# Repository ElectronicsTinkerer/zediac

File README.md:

# ZEDIA Computer System

(Zach's Electronic Desktop Instrumentation and Analysis Computer)

![Top-down photo of the PCB. From left to right: GPIO connector, VIA, CPU, RAM, ROM, DUART. Below the CPU RAM and ROM are several 74xx series ICs for address decoding. The right edge of the PCB features the power and USB connectors. Note the incorrect date on the PCB-when I changed the date over from December, 2022 to January 2023, I managed to change the month and date, but not the year. Oops](./pcb1.0.jpg)

## System stats

* W65C816 CPU
* 32k EEPROM (with write capability)
* 512K RAM
* 65C22 VIA, providing ~20 GPIOs (really 16 + 4 handshake lines)
* ST16C2752 Dual UART
* 5+ MHz operation
* Partial system bus expansion header with address decoding
* USB-C UART interface via a CP2102
* 2 power delivery methods (unregulated voltage in via barrel jack or terminal block. Also power over USB)
* ESD protection on all IO headers

## Software

All software is available in the `software` directory. At the moment, there is a system monitor which provides many memory manipulation utilities.

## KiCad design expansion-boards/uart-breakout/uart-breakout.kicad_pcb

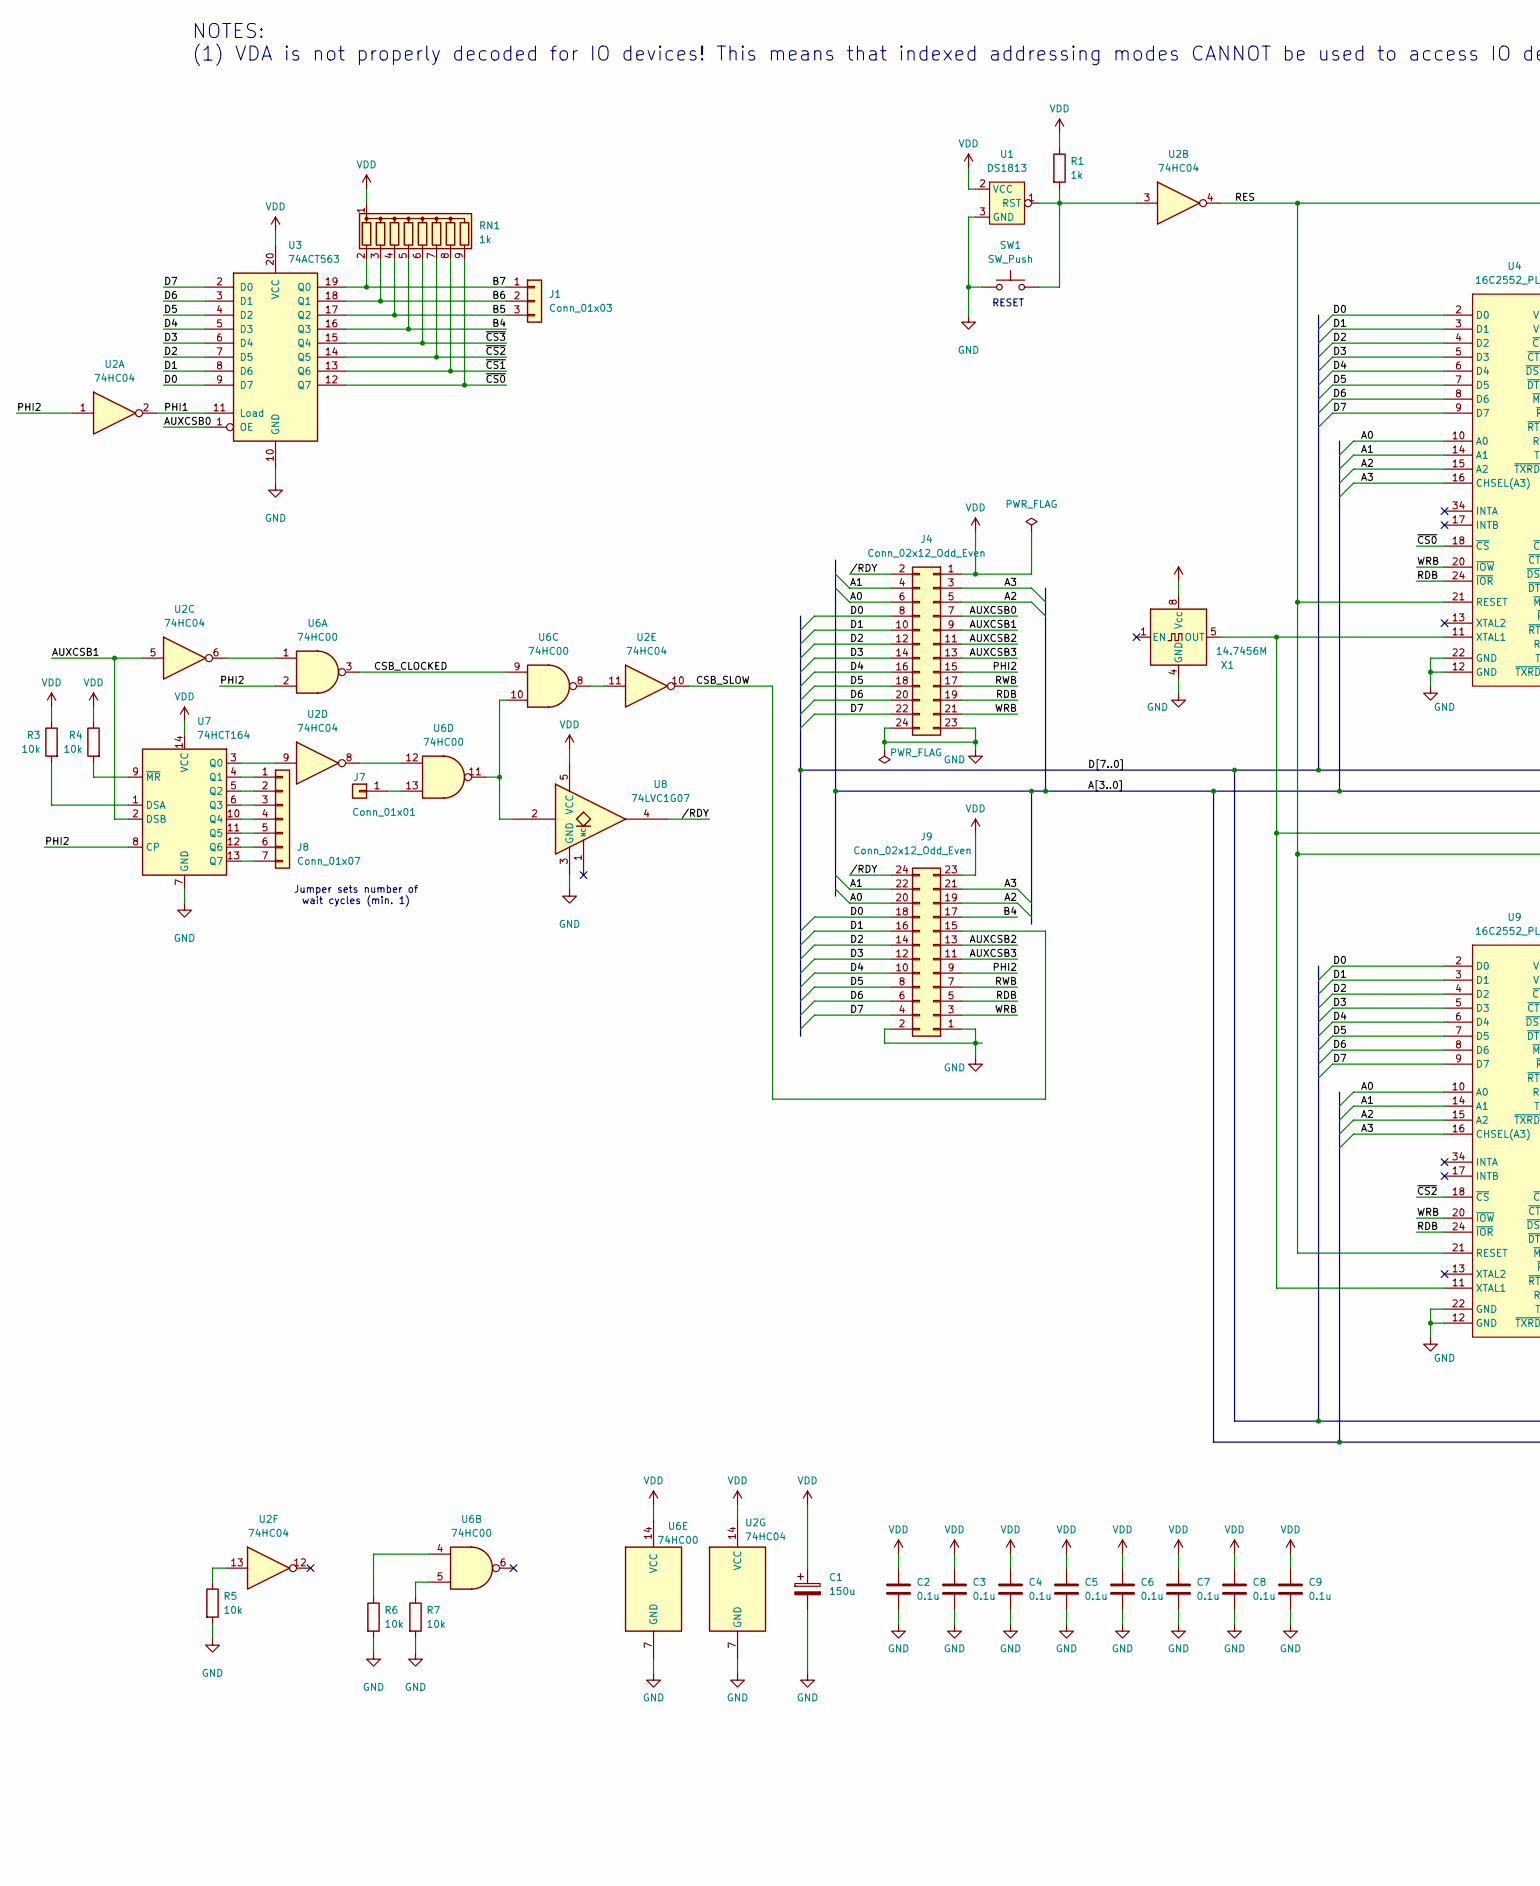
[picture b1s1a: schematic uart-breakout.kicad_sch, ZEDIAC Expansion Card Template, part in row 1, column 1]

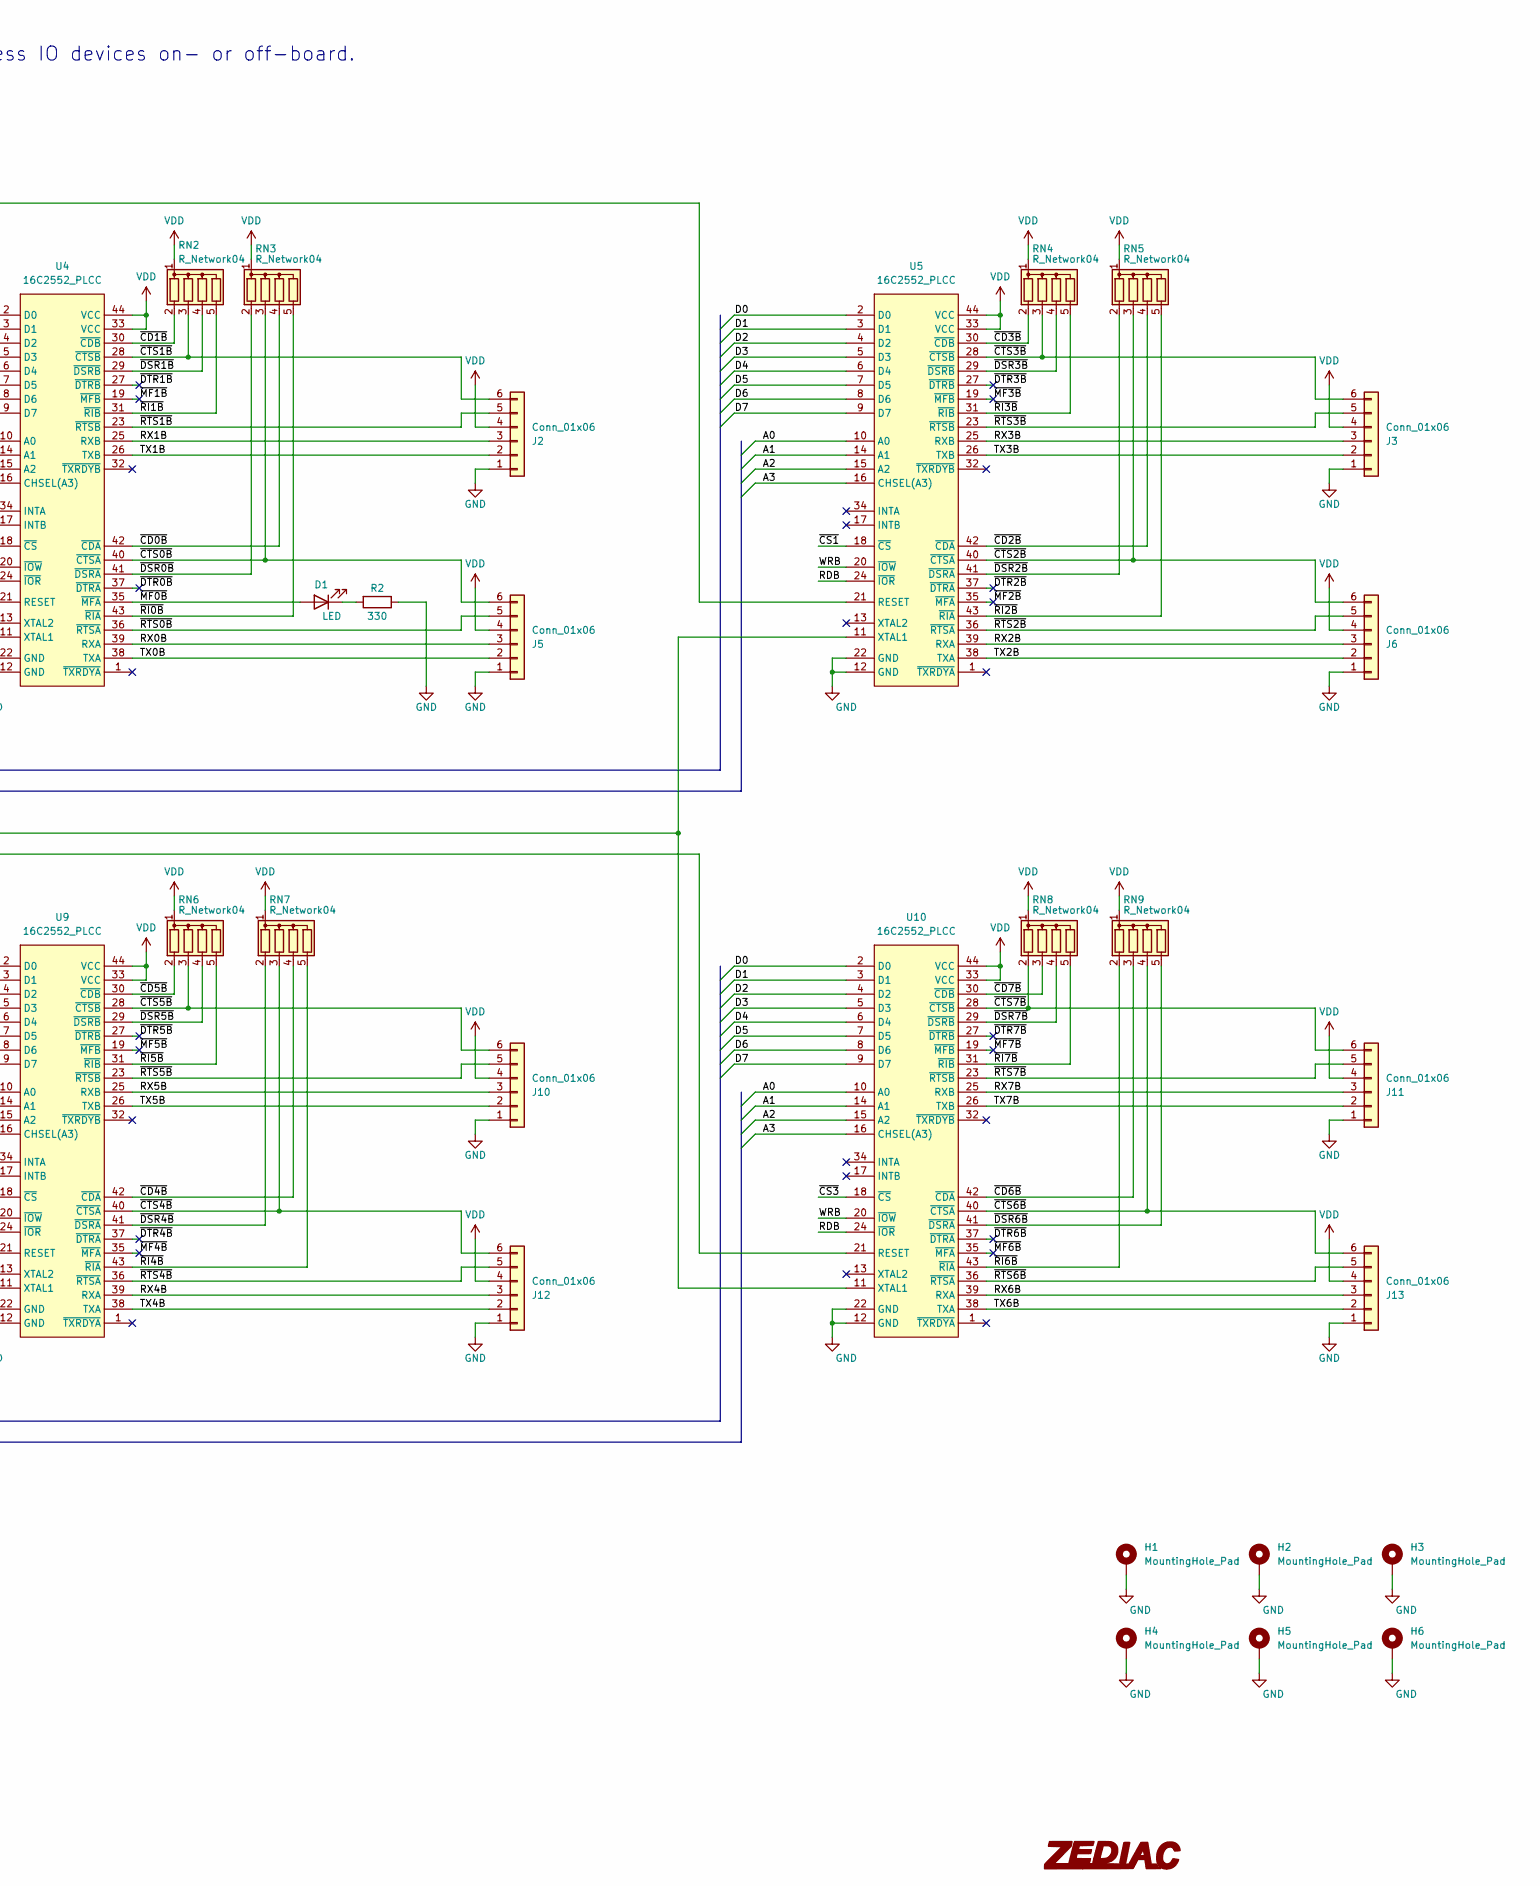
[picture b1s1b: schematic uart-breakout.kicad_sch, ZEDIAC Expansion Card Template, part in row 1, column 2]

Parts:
C1: 150u; C_Radial_D8.0mm_H7.0mm_P3.50mm
C2, C3, C4, C5, C6, C7, C8, C9: 0.1u; C_Disc_D4.3mm_W1.9mm_P5.00mm
D1: LED; LED_D5.0mm
G1: LOGO; zediac-logo
H1, H2, H3, H4, H5, H6: MountingHole_Pad; MountingHole_3.2mm_M3_Pad
J1: Conn_01x03; PinSocket_1x03_P2.54mm_Vertical
J2, J3, J5, J6, J10, J11, J12, J13: Conn_01x06; PinSocket_1x06_P2.54mm_Vertical
J4, J9: Conn_02x12_Odd_Even; PinSocket_2x12_P2.54mm_Vertical
J7: Conn_01x01; PinSocket_1x01_P2.54mm_Vertical
J8: Conn_01x07; PinSocket_1x07_P2.54mm_Vertical
R1: 1k; R_Axial_DIN0207_L6.3mm_D2.5mm_P7.62mm_Horizontal
R2: 330; R_Axial_DIN0207_L6.3mm_D2.5mm_P7.62mm_Horizontal
R3, R4, R5, R6, R7: 10k; R_Axial_DIN0207_L6.3mm_D2.5mm_P7.62mm_Horizontal
RN1: 1k; R_Array_SIP9
RN2, RN3, RN4, RN5, RN6, RN7, RN8, RN9: R_Network04; R_Array_SIP5
SW1: SW_Push; SW_PUSH_6mm
U1: DS1813; TO-92L_Wide
U2: 74HC04; DIP-14_W7.62mm
U3: 74ACT563; DIP-20_W7.62mm
U4, U5, U9, U10: 16C2552_PLCC; PLCC-44_THT-Socket
U6: 74HC00; DIP-14_W7.62mm
U7: 74HCT164; DIP-14_W7.62mm
U8: 74LVC1G07; SOT-353_SC-70-5_Handsoldering
X1: 14.7456M; Oscillator_DIP-8

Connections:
/A0: J4.6, J9.20, U4.10 (A0), U5.10 (A0), U9.10 (A0), U10.10 (A0)
/A1: J4.4, J9.22, U4.14 (A1), U5.14 (A1), U9.14 (A1), U10.14 (A1)
/A2: J4.5, J9.19, U4.15 (A2), U5.15 (A2), U9.15 (A2), U10.15 (A2)
/A3: J4.3, J9.21, U4.16 (CHSEL(A3)), U5.16 (CHSEL(A3)), U9.16 (CHSEL(A3)), U10.16 (CHSEL(A3))
/AUXCSB0: J4.7, U3.1 (OE)
/AUXCSB1: J4.9, U2.5, U7.2 (DSB)
/AUXCSB2: J4.11, J9.13
/AUXCSB3: J4.13, J9.11
/B4: J9.17, RN1.5 (R4), U3.16 (Q3)
/B5: J1.3, RN1.4 (R3), U3.17 (Q2)
/B6: J1.2, RN1.3 (R2), U3.18 (Q1)
/B7: J1.1, RN1.2 (R1), U3.19 (Q0)
/CSB_CLOCKED: U6.3, U6.9
/CSB_SLOW: J9.15, U2.10
/D0: J4.8, J9.18, U3.9 (D7), U4.2 (D0), U5.2 (D0), U9.2 (D0), U10.2 (D0)
/D1: J4.10, J9.16, U3.8 (D6), U4.3 (D1), U5.3 (D1), U9.3 (D1), U10.3 (D1)
/D2: J4.12, J9.14, U3.7 (D5), U4.4 (D2), U5.4 (D2), U9.4 (D2), U10.4 (D2)
/D3: J4.14, J9.12, U3.6 (D4), U4.5 (D3), U5.5 (D3), U9.5 (D3), U10.5 (D3)
/D4: J4.16, J9.10, U3.5 (D3), U4.6 (D4), U5.6 (D4), U9.6 (D4), U10.6 (D4)
/D5: J4.18, J9.8, U3.4 (D2), U4.7 (D5), U5.7 (D5), U9.7 (D5), U10.7 (D5)
/D6: J4.20, J9.6, U3.3 (D1), U4.8 (D6), U5.8 (D6), U9.8 (D6), U10.8 (D6)
/D7: J4.22, J9.4, U3.2 (D0), U4.9 (D7), U5.9 (D7), U9.9 (D7), U10.9 (D7)
/PHI1: U2.2, U3.11 (Load)
/PHI2: J4.15, J9.9, U2.1, U6.2, U7.8 (CP)
/RDB: J4.19, J9.5, U4.24 (~IOR), U5.24 (~IOR), U9.24 (~IOR), U10.24 (~IOR)
/RES: U2.4, U4.21 (RESET), U5.21 (RESET), U9.21 (RESET), U10.21 (RESET)
/RWB: J4.17, J9.7
/RX0B: J5.3, U4.39 (RXA)
/RX1B: J2.3, U4.25 (RXB)
/RX2B: J6.3, U5.39 (RXA)
/RX3B: J3.3, U5.25 (RXB)
/RX4B: J12.3, U9.39 (RXA)
/RX5B: J10.3, U9.25 (RXB)
/RX6B: J13.3, U10.39 (RXA)
/RX7B: J11.3, U10.25 (RXB)
/TX0B: J5.2, U4.38 (TXA)
/TX1B: J2.2, U4.26 (TXB)
/TX2B: J6.2, U5.38 (TXA)
/TX3B: J3.2, U5.26 (TXB)
/TX4B: J12.2, U9.38 (TXA)
/TX5B: J10.2, U9.26 (TXB)
/TX6B: J13.2, U10.38 (TXA)
/TX7B: J11.2, U10.26 (TXB)
/WRB: J4.21, J9.3, U4.20 (~IOW), U5.20 (~IOW), U9.20 (~IOW), U10.20 (~IOW)
//RDY: J4.2, J9.24, U8.4
/~CD0B: RN3.4 (R3), U4.42 (~CDA)
/~CD1B: RN2.2 (R1), U4.30 (~CDB)
/~CD2B: RN5.4 (R3), U5.42 (~CDA)
/~CD3B: RN4.2 (R1), U5.30 (~CDB)
/~CD4B: RN7.4 (R3), U9.42 (~CDA)
/~CD5B: RN6.2 (R1), U9.30 (~CDB)
/~CD6B: RN9.3 (R2), U10.42 (~CDA)
/~CD7B: RN8.3 (R2), U10.30 (~CDB)
/~CS0: RN1.9 (R8), U3.12 (Q7), U4.18 (~CS)
/~CS1: RN1.8 (R7), U3.13 (Q6), U5.18 (~CS)
/~CS2: RN1.7 (R6), U3.14 (Q5), U9.18 (~CS)
/~CS3: RN1.6 (R5), U3.15 (Q4), U10.18 (~CS)
/~CTS0B: J5.6, RN3.3 (R2), U4.40 (~CTSA)
/~CTS1B: J2.6, RN2.3 (R2), U4.28 (~CTSB)
/~CTS2B: J6.6, RN5.3 (R2), U5.40 (~CTSA)
/~CTS3B: J3.6, RN4.3 (R2), U5.28 (~CTSB)
/~CTS4B: J12.6, RN7.3 (R2), U9.40 (~CTSA)
/~CTS5B: J10.6, RN6.3 (R2), U9.28 (~CTSB)
/~CTS6B: J13.6, RN9.4 (R3), U10.40 (~CTSA)
/~CTS7B: J11.6, RN8.2 (R1), U10.28 (~CTSB)
/~DSR0B: RN3.2 (R1), U4.41 (~DSRA)
/~DSR1B: RN2.4 (R3), U4.29 (~DSRB)
/~DSR2B: RN5.2 (R1), U5.41 (~DSRA)
/~DSR3B: RN4.4 (R3), U5.29 (~DSRB)
/~DSR4B: RN7.2 (R1), U9.41 (~DSRA)
/~DSR5B: RN6.4 (R3), U9.29 (~DSRB)
/~DSR6B: RN9.5 (R4), U10.41 (~DSRA)
/~DSR7B: RN8.4 (R3), U10.29 (~DSRB)
/~DTR0B: U4.37 (~DTRA)
/~DTR1B: U4.27 (~DTRB)
/~DTR2B: U5.37 (~DTRA)
/~DTR3B: U5.27 (~DTRB)
/~DTR4B: U9.37 (~DTRA)
/~DTR5B: U9.27 (~DTRB)
/~DTR6B: U10.37 (~DTRA)
/~DTR7B: U10.27 (~DTRB)
/~MF0B: D1.2 (A), U4.35 (~MFA)
/~MF1B: U4.19 (~MFB)
/~MF2B: U5.35 (~MFA)
/~MF3B: U5.19 (~MFB)
/~MF4B: U9.35 (~MFA)
/~MF5B: U9.19 (~MFB)
/~MF6B: U10.35 (~MFA)
/~MF7B: U10.19 (~MFB)
/~RI0B: RN3.5 (R4), U4.43 (~RIA)
/~RI1B: RN2.5 (R4), U4.31 (~RIB)
/~RI2B: RN5.5 (R4), U5.43 (~RIA)
/~RI3B: RN4.5 (R4), U5.31 (~RIB)
/~RI4B: RN7.5 (R4), U9.43 (~RIA)
/~RI5B: RN6.5 (R4), U9.31 (~RIB)
/~RI6B: RN9.2 (R1), U10.43 (~RIA)
/~RI7B: RN8.5 (R4), U10.31 (~RIB)
/~RTS0B: J5.5, U4.36 (~RTSA)
/~RTS1B: J2.5, U4.23 (~RTSB)
/~RTS2B: J6.5, U5.36 (~RTSA)
/~RTS3B: J3.5, U5.23 (~RTSB)
/~RTS4B: J12.5, U9.36 (~RTSA)
/~RTS5B: J10.5, U9.23 (~RTSB)
/~RTS6B: J13.5, U10.36 (~RTSA)
/~RTS7B: J11.5, U10.23 (~RTSB)
GND: C1.2, C2.2, C3.2, C4.2, C5.2, C6.2, C7.2, C8.2, C9.2, H1.1, H2.1, H3.1, H4.1, H5.1, H6.1, J2.1, J3.1, J4.23, J4.24, J5.1, J6.1, J9.1, J9.2, J10.1, J11.1, J12.1, J13.1, R2.1, R5.2, R6.2, R7.2, SW1.1, U1.3 (GND), U2.7 (GND), U3.10 (GND), U4.12 (GND), U4.22 (GND), U5.12 (GND), U5.22 (GND), U6.7 (GND), U7.7 (GND), U8.3 (GND), U9.12 (GND), U9.22 (GND), U10.12 (GND), U10.22 (GND), X1.4 (GND)
unnamed: D1.1 (K), R2.2
unnamed: J7.1, U6.13
unnamed: J8.1, U7.4 (Q1)
unnamed: J8.2, U7.5 (Q2)
unnamed: J8.3, U7.6 (Q3)
unnamed: J8.4, U7.10 (Q4)
unnamed: J8.5, U7.11 (Q5)
unnamed: J8.6, U7.12 (Q6)
unnamed: J8.7, U7.13 (Q7)
unnamed: R5.1, U2.13
unnamed: R6.1, U6.4
unnamed: R7.1, U6.5
unnamed: R1.2, SW1.2, U1.1 (RST), U2.3
unnamed: U2.6, U6.1
unnamed: U2.8, U6.12
unnamed: U2.11, U6.8
unnamed: U6.10, U6.11, U8.2
unnamed: R3.2, U7.1 (DSA)
unnamed: U2.9, U7.3 (Q0)
unnamed: R4.2, U7.9 (~MR)
unnamed: U4.11 (XTAL1), U5.11 (XTAL1), U9.11 (XTAL1), U10.11 (XTAL1), X1.5 (OUT)
VDD: C1.1, C2.1, C3.1, C4.1, C5.1, C6.1, C7.1, C8.1, C9.1, J2.4, J3.4, J4.1, J5.4, J6.4, J9.23, J10.4, J11.4, J12.4, J13.4, R1.1, R3.1, R4.1, RN1.1 (common), RN2.1 (common), RN3.1 (common), RN4.1 (common), RN5.1 (common), RN6.1 (common), RN7.1 (common), RN8.1 (common), RN9.1 (common), U1.2 (VCC), U2.14 (VCC), U3.20 (VCC), U4.33 (VCC), U4.44 (VCC), U5.33 (VCC), U5.44 (VCC), U6.14 (VCC), U7.14 (VCC), U8.5 (VCC), U9.33 (VCC), U9.44 (VCC), U10.33 (VCC), U10.44 (VCC), X1.8 (Vcc)

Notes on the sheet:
RESET
Jumper sets number of wait cycles (min. 1)
NOTES: (1) VDA is not properly decoded for IO devices! This means that indexed addressing modes CANNOT be used to access IO devices on- or off-board.

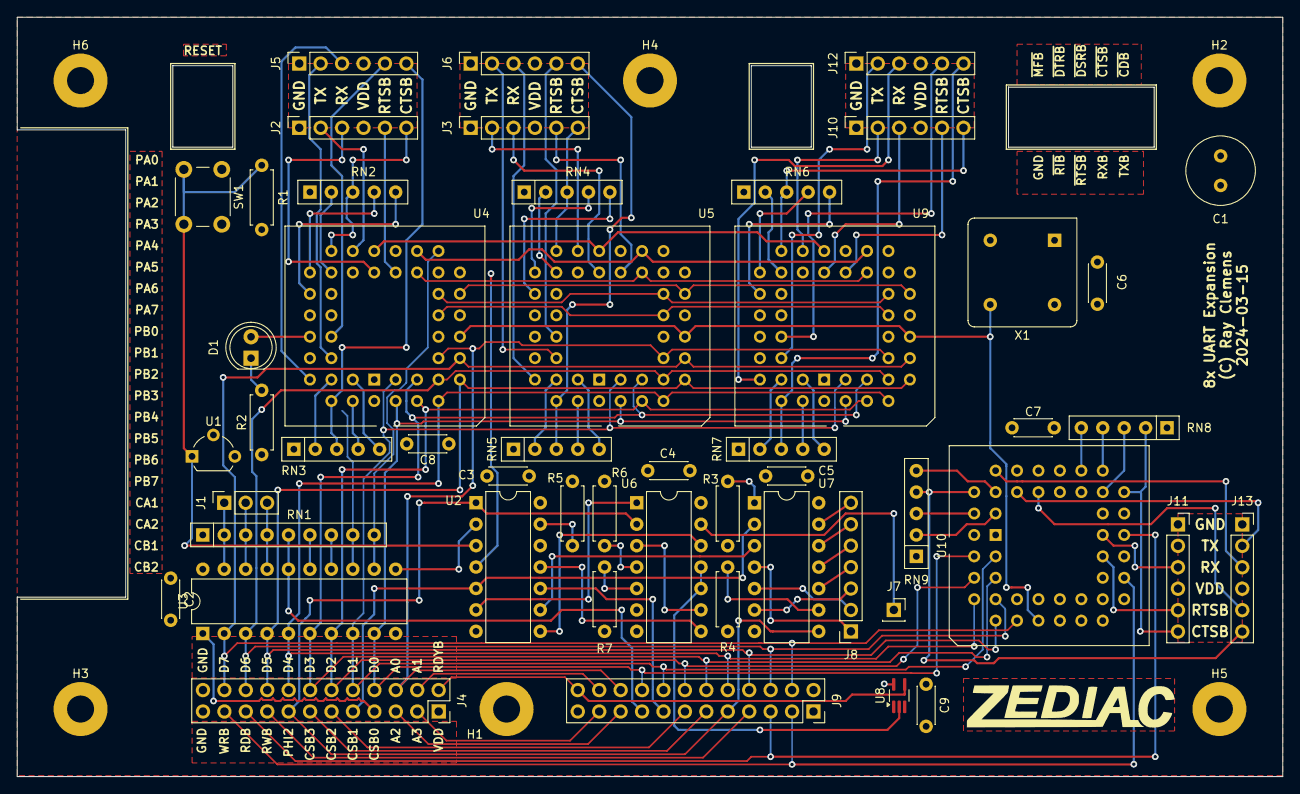
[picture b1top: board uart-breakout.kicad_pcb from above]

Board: 4 copper layers, 150.0 x 90.0 mm, 58 parts (0 on the bottom side), 113 nets.

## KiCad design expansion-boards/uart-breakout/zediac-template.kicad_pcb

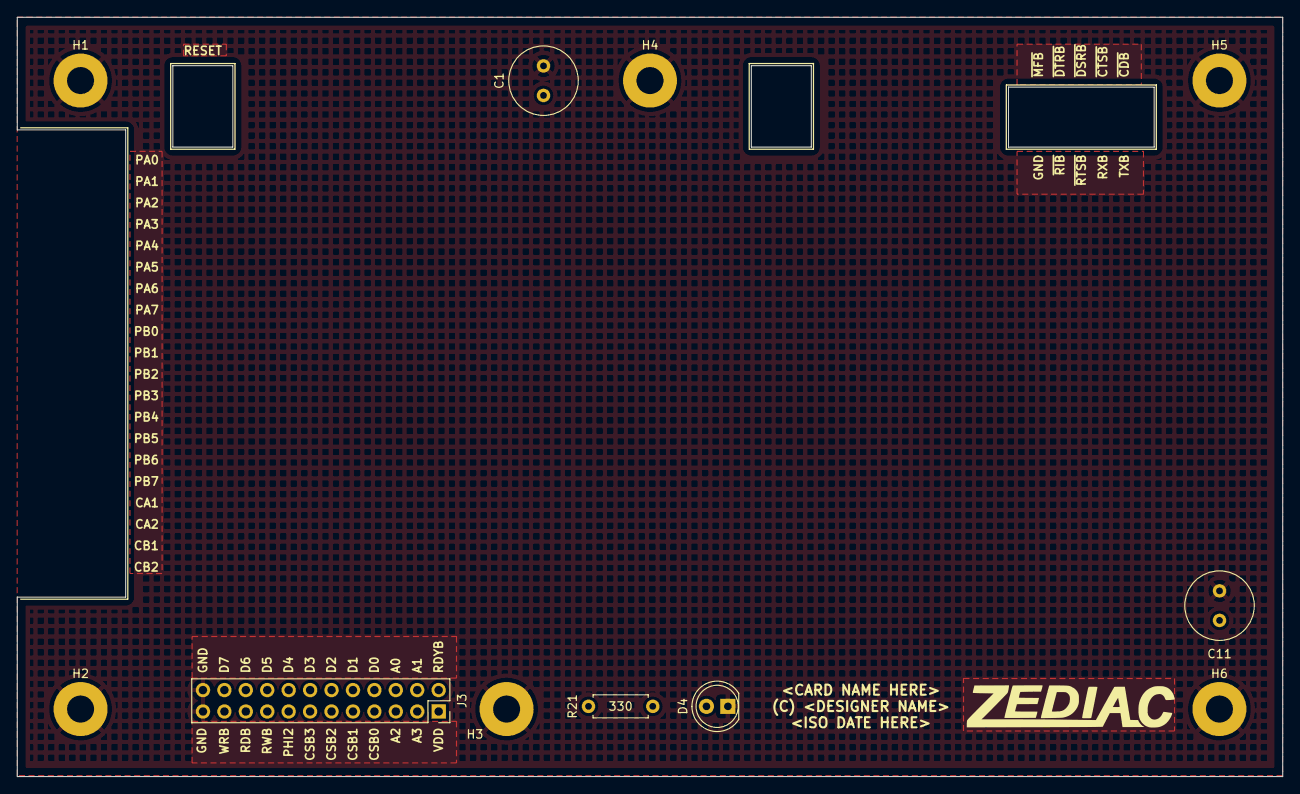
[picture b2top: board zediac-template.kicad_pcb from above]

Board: 4 copper layers, 150.0 x 90.0 mm, 12 parts (0 on the bottom side), 3 nets, no tracks yet.

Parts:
C1, C11: 150u; C_Radial_D8.0mm_H7.0mm_P3.50mm
D4: LED; LED_D5.0mm
G1: LOGO; zediac-logo
H1, H2, H3, H4, H5, H6: MountingHole_Pad; MountingHole_3.2mm_M3_Pad
J3: Conn_02x12_Odd_Even; PinSocket_2x12_P2.54mm_Vertical
R21: 330; R_Axial_DIN0207_L6.3mm_D2.5mm_P7.62mm_Horizontal

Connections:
GND: C1.2, C11.2, D4.1 (K), H1.1, H2.1, H3.1, H4.1, H5.1, H6.1, J3.23, J3.24
unnamed: D4.2 (A), R21.2
VDD: C1.1, C11.1, J3.1, R21.1

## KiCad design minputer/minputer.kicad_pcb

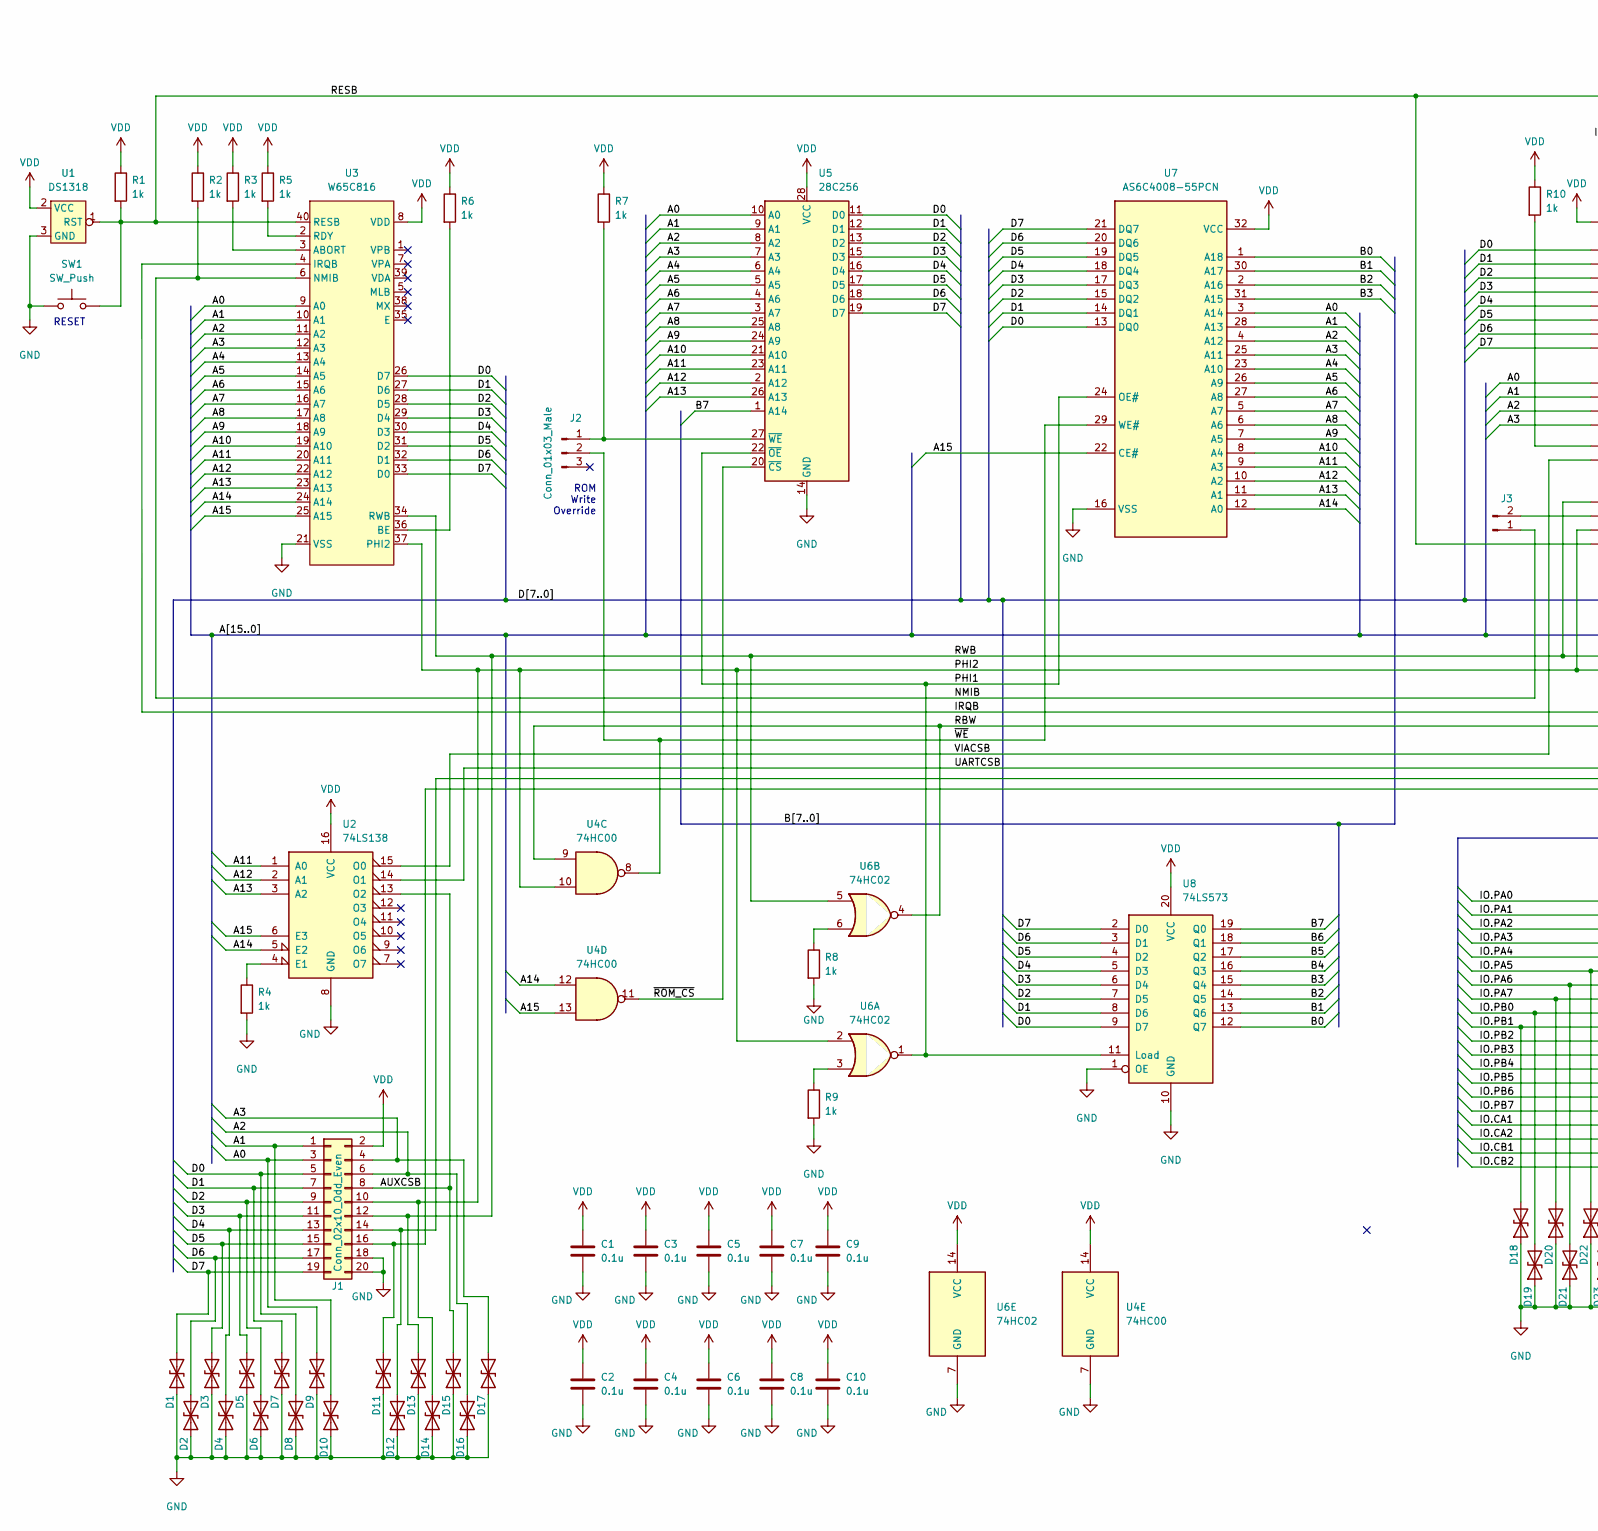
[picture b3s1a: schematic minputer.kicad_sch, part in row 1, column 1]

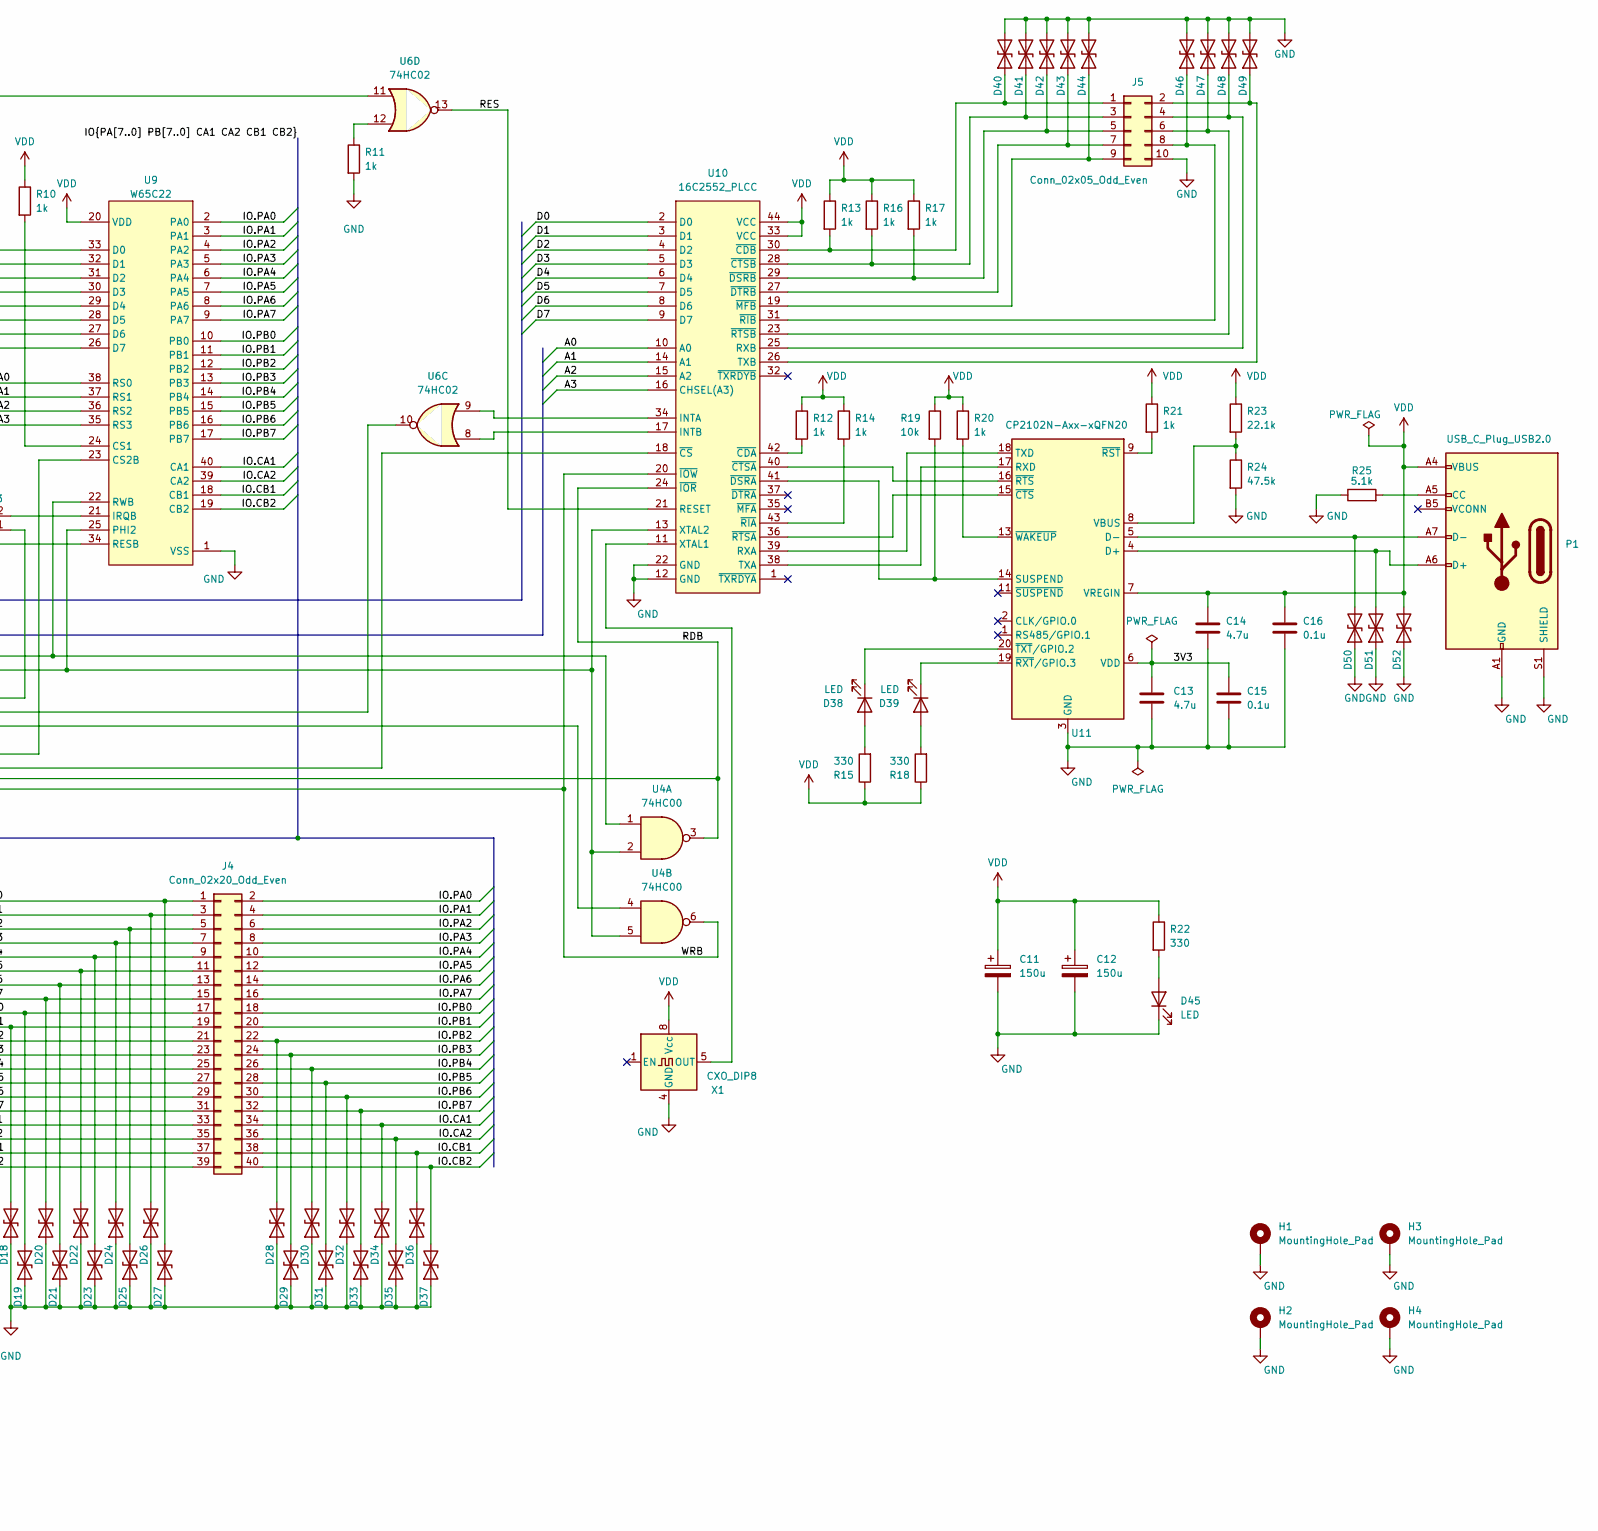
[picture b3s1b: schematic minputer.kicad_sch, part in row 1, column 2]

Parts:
C1, C2, C3, C4, C5, C6, C7, C8, C9, C10: 0.1u; C_Disc_D4.3mm_W1.9mm_P5.00mm
C11, C12: 150u; C_Radial_D8.0mm_H7.0mm_P3.50mm
C13, C14: 4.7u; C_0603_1608Metric_Pad1.08x0.95mm_HandSolder
C15, C16: 0.1u; C_0603_1608Metric_Pad1.08x0.95mm_HandSolder
D1, D2, D3, D4, D5, D6, D7, D8, D9, D10, D11, D12, D13, D14, D15, D16, D17, D18, D19, D20, D21, D22, D23, D24, D25, D26, D27, D28, D29, D30, D31, D32, D33, D34, D35, D36, D37, D40, D41, D42, D43, D44, D46, D47, D48, D49, D50, D51, D52: D_TVS; D_0603_1608Metric_Pad1.05x0.95mm_HandSolder
D38, D39, D45: LED; LED_D5.0mm
H1, H2, H3, H4: MountingHole_Pad; MountingHole_4.3mm_M4_DIN965_Pad
J1: Conn_02x10_Odd_Even; PinHeader_2x10_P2.54mm_Vertical
J2: Conn_01x03_Male; PinHeader_1x03_P2.54mm_Vertical
J3: Conn_01x02_Male; PinHeader_1x02_P2.54mm_Vertical
J4: Conn_02x20_Odd_Even; PinHeader_2x20_P2.54mm_Vertical
J5: Conn_02x05_Odd_Even; PinHeader_2x05_P2.54mm_Vertical
P1: USB_C_Plug_USB2.0; USB_C_Receptacle_Amphenol_12401548E4-2A
R1, R2, R3, R4, R5, R6, R7, R8, R9, R10, R11, R12, R13, R14, R16, R17, R20, R21: 1k; R_Axial_DIN0207_L6.3mm_D2.5mm_P7.62mm_Horizontal
R15, R18, R22: 330; R_Axial_DIN0207_L6.3mm_D2.5mm_P7.62mm_Horizontal
R19: 10k; R_Axial_DIN0207_L6.3mm_D2.5mm_P7.62mm_Horizontal
R23: 22.1k; R_0603_1608Metric_Pad0.98x0.95mm_HandSolder
R24: 47.5k; R_0603_1608Metric_Pad0.98x0.95mm_HandSolder
R25: 5.1k; R_0603_1608Metric_Pad0.98x0.95mm_HandSolder
SW1: SW_Push; SW_PUSH_6mm
U1: DS1318; TO-92L_HandSolder
U2: 74LS138; DIP-16_W7.62mm
U3: W65C816; DIP-40_W15.24mm
U4: 74HC00; DIP-14_W7.62mm
U5: 28C256; DIP-28_W15.24mm
U6: 74HC02; DIP-14_W7.62mm
U7: AS6C4008-55PCN; DIP-32_W15.24mm
U8: 74LS573; DIP-20_W7.62mm
U9: W65C22; DIP-40_W15.24mm
U10: 16C2552_PLCC; PLCC-44_THT-Socket
U11: CP2102N-Axx-xQFN20; VQFN-20-1EP_3x3mm_P0.45mm_EP1.55x1.55mm
X1: CXO_DIP8; Oscillator_DIP-8

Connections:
/3V3: C13.1, C15.1, U11.6 (VDD)
/A0: D9.2 (A2), J1.3, U3.9 (A0), U5.10 (A0), U7.3 (A14), U9.38 (RS0), U10.10 (A0)
/A1: D10.2 (A2), J1.1, U3.10 (A1), U5.9 (A1), U7.28 (A13), U9.37 (RS1), U10.14 (A1)
/A2: D16.2 (A2), J1.6, U3.11 (A2), U5.8 (A2), U7.4 (A12), U9.36 (RS2), U10.15 (A2)
/A3: D17.2 (A2), J1.4, U3.12 (A3), U5.7 (A3), U7.25 (A11), U9.35 (RS3), U10.16 (CHSEL(A3))
/A4: U3.13 (A4), U5.6 (A4), U7.23 (A10)
/A5: U3.14 (A5), U5.5 (A5), U7.26 (A9)
/A6: U3.15 (A6), U5.4 (A6), U7.27 (A8)
/A7: U3.16 (A7), U5.3 (A7), U7.5 (A7)
/A8: U3.17 (A8), U5.25 (A8), U7.6 (A6)
/A9: U3.18 (A9), U5.24 (A9), U7.7 (A5)
/A10: U3.19 (A10), U5.21 (A10), U7.8 (A4)
/A11: U2.1 (A0), U3.20 (A11), U5.23 (A11), U7.9 (A3)
/A12: U2.2 (A1), U3.22 (A12), U5.2 (A12), U7.10 (A2)
/A13: U2.3 (A2), U3.23 (A13), U5.26 (A13), U7.11 (A1)
/A14: U2.5 (E2), U3.24 (A14), U4.12, U7.12 (A0)
/A15: U2.6 (E3), U3.25 (A15), U4.13, U7.22 (CE#)
/AUXCSB: D15.2 (A2), J1.8, U2.13 (O2)
/B0: U7.1 (A18), U8.12 (Q7)
/B1: U7.30 (A17), U8.13 (Q6)
/B2: U7.2 (A16), U8.14 (Q5)
/B3: U7.31 (A15), U8.15 (Q4)
/B4: U8.16 (Q3)
/B5: U8.17 (Q2)
/B6: U8.18 (Q1)
/B7: U5.1 (A14), U8.19 (Q0)
/D0: D8.2 (A2), J1.5, U3.26 (D7), U5.11 (D0), U7.13 (DQ0), U8.9 (D7), U9.33 (D0), U10.2 (D0)
/D1: D7.2 (A2), J1.7, U3.27 (D6), U5.12 (D1), U7.14 (DQ1), U8.8 (D6), U9.32 (D1), U10.3 (D1)
/D2: D6.2 (A2), J1.9, U3.28 (D5), U5.13 (D2), U7.15 (DQ2), U8.7 (D5), U9.31 (D2), U10.4 (D2)
/D3: D5.2 (A2), J1.11, U3.29 (D4), U5.15 (D3), U7.17 (DQ3), U8.6 (D4), U9.30 (D3), U10.5 (D3)
/D4: D4.2 (A2), J1.13, U3.30 (D3), U5.16 (D4), U7.18 (DQ4), U8.5 (D3), U9.29 (D4), U10.6 (D4)
/D5: D3.2 (A2), J1.15, U3.31 (D2), U5.17 (D5), U7.19 (DQ5), U8.4 (D2), U9.28 (D5), U10.7 (D5)
/D6: D2.2 (A2), J1.17, U3.32 (D1), U5.18 (D6), U7.20 (DQ6), U8.3 (D1), U9.27 (D6), U10.8 (D6)
/D7: D1.2 (A2), J1.19, U3.33 (D0), U5.19 (D7), U7.21 (DQ7), U8.2 (D0), U9.26 (D7), U10.9 (D7)
/IO.CA1: D34.2 (A2), J4.33, J4.34, U9.40 (CA1)
/IO.CA2: D35.2 (A2), J4.35, J4.36, U9.39 (CA2)
/IO.CB1: D36.2 (A2), J4.37, J4.38, U9.18 (CB1)
/IO.CB2: D37.2 (A2), J4.39, J4.40, U9.19 (CB2)
/IO.PA0: D27.2 (A2), J4.1, J4.2, U9.2 (PA0)
/IO.PA1: D26.2 (A2), J4.3, J4.4, U9.3 (PA1)
/IO.PA2: D25.2 (A2), J4.5, J4.6, U9.4 (PA2)
/IO.PA3: D24.2 (A2), J4.7, J4.8, U9.5 (PA3)
/IO.PA4: D23.2 (A2), J4.9, J4.10, U9.6 (PA4)
/IO.PA5: D22.2 (A2), J4.11, J4.12, U9.7 (PA5)
/IO.PA6: D21.2 (A2), J4.13, J4.14, U9.8 (PA6)
/IO.PA7: D20.2 (A2), J4.15, J4.16, U9.9 (PA7)
/IO.PB0: D19.2 (A2), J4.17, J4.18, U9.10 (PB0)
/IO.PB1: D18.2 (A2), J4.19, J4.20, U9.11 (PB1)
/IO.PB2: D28.2 (A2), J4.21, J4.22, U9.12 (PB2)
/IO.PB3: D29.2 (A2), J4.23, J4.24, U9.13 (PB3)
/IO.PB4: D30.2 (A2), J4.25, J4.26, U9.14 (PB4)
/IO.PB5: D31.2 (A2), J4.27, J4.28, U9.15 (PB5)
/IO.PB6: D32.2 (A2), J4.29, J4.30, U9.16 (PB6)
/IO.PB7: D33.2 (A2), J4.31, J4.32, U9.17 (PB7)
/IRQB: U3.4 (IRQB), U6.10
/NMIB: J3.1, R2.2, U3.6 (NMIB)
/PHI1: U5.22 (~OE), U6.1, U7.24 (OE#), U8.11 (Load)
/PHI2: D14.2 (A2), J1.10, U3.37 (PHI2), U4.2, U4.5, U4.10, U6.2, U9.25 (PHI2), U10.13 (XTAL2)
/RBW: U4.4, U4.9, U6.4
/RDB: D12.2 (A2), J1.14, U4.3, U10.24 (~IOR)
/RES: U6.13, U10.21 (RESET)
/RESB: R1.2, SW1.2, U1.1 (RST), U3.40 (RESB), U6.11, U9.34 (RESB)
/RWB: D13.2 (A2), J1.12, U3.34 (RWB), U4.1, U6.5, U9.22 (RWB)
/UARTCSB: U2.14 (O1), U10.18 (~CS)
/VIACSB: U2.15 (O0), U9.23 (CS2B)
/WRB: D11.2 (A2), J1.16, U4.6, U10.20 (~IOW)
/~ROM_CS: U4.11, U5.20 (~CS)
/~WE: J2.2, U4.8, U7.29 (WE#)
GND: C1.2, C2.2, C3.2, C4.2, C5.2, C6.2, C7.2, C8.2, C9.2, C10.2, C11.2, C12.2, C13.2, C14.2, C15.2, C16.2, D1.1 (A1), D2.1 (A1), D3.1 (A1), D4.1 (A1), D5.1 (A1), D6.1 (A1), D7.1 (A1), D8.1 (A1), D9.1 (A1), D10.1 (A1), D11.1 (A1), D12.1 (A1), D13.1 (A1), D14.1 (A1), D15.1 (A1), D16.1 (A1), D17.1 (A1), D18.1 (A1), D19.1 (A1), D20.1 (A1), D21.1 (A1), D22.1 (A1), D23.1 (A1), D24.1 (A1), D25.1 (A1), D26.1 (A1), D27.1 (A1), D28.1 (A1), D29.1 (A1), D30.1 (A1), D31.1 (A1), D32.1 (A1), D33.1 (A1), D34.1 (A1), D35.1 (A1), D36.1 (A1), D37.1 (A1), D40.2 (A2), D41.2 (A2), D42.2 (A2), D43.2 (A2), D44.2 (A2), D45.1 (K), D46.2 (A2), D47.2 (A2), D48.2 (A2), D49.2 (A2), D50.1 (A1), D51.1 (A1), D52.1 (A1), H1.1, H2.1, H3.1, H4.1, J1.18, J1.20, J5.10, P1.A1 (GND), P1.A12 (GND), P1.B1 (GND), P1.B12 (GND), P1.S1 (SHIELD), R4.2, R8.2, R9.2, R11.2, R24.2, R25.1, SW1.1, U1.3 (GND), U2.8 (GND), U3.21 (VSS), U4.7 (GND), U5.14 (GND), U6.7 (GND), U7.16 (VSS), U8.1 (OE), U8.10 (GND), U9.1 (VSS), U10.12 (GND), U10.22 (GND), U11.3 (GND), U11.12 (GND), U11.21 (GND), X1.4 (GND)
unnamed: D38.1 (K), U11.20 (~TXT/GPIO.2)
unnamed: D38.2 (A), R15.2
unnamed: D39.1 (K), U11.19 (~RXT/GPIO.3)
unnamed: D39.2 (A), R18.2
unnamed: D40.1 (A1), J5.1, R13.2, U10.30 (~CDB)
unnamed: D41.1 (A1), J5.3, R16.2, U10.28 (~CTSB)
unnamed: D42.1 (A1), J5.5, R17.2, U10.29 (~DSRB)
unnamed: D43.1 (A1), J5.7, U10.27 (~DTRB)
unnamed: D44.1 (A1), J5.9, U10.19 (~MFB)
unnamed: D45.2 (A), R22.2
unnamed: D46.1 (A1), J5.8, U10.31 (~RIB)
unnamed: D47.1 (A1), J5.6, U10.23 (~RTSB)
unnamed: D48.1 (A1), J5.4, U10.25 (RXB)
unnamed: D49.1 (A1), J5.2, U10.26 (TXB)
unnamed: D50.2 (A2), P1.A7 (D-), U11.5 (D-)
unnamed: D51.2 (A2), P1.A6 (D+), U11.4 (D+)
unnamed: J2.1, R7.2, U5.27 (~WE)
unnamed: J3.2, U9.21 (IRQB)
unnamed: P1.A5 (CC), R25.2
unnamed: R3.2, U3.3 (ABORT)
unnamed: R4.1, U2.4 (E1)
unnamed: R5.2, U3.2 (RDY)
unnamed: R6.2, U3.36 (BE)
unnamed: R8.1, U6.6
unnamed: R9.1, U6.3
unnamed: R10.2, U9.24 (CS1)
unnamed: R11.1, U6.12
unnamed: R12.2, U10.42 (~CDA)
unnamed: R14.2, U10.43 (~RIA)
unnamed: R19.2, U10.41 (~DSRA), U11.14 (SUSPEND)
unnamed: R20.2, U11.13 (~WAKEUP)
unnamed: R21.2, U11.9 (~RST)
unnamed: R23.2, R24.1, U11.8 (VBUS)
unnamed: U10.11 (XTAL1), X1.5 (OUT)
unnamed: U6.8, U10.17 (INTB)
unnamed: U6.9, U10.34 (INTA)
unnamed: U10.36 (~RTSA), U11.15 (~CTS)
unnamed: U10.38 (TXA), U11.17 (RXD)
unnamed: U10.39 (RXA), U11.18 (TXD)
unnamed: U10.40 (~CTSA), U11.16 (~RTS)
VDD: C1.1, C2.1, C3.1, C4.1, C5.1, C6.1, C7.1, C8.1, C9.1, C10.1, C11.1, C12.1, C14.1, C16.1, D52.2 (A2), J1.2, P1.A4 (VBUS), P1.A9 (VBUS), P1.B4 (VBUS), P1.B9 (VBUS), R1.1, R2.1, R3.1, R5.1, R6.1, R7.1, R10.1, R12.1, R13.1, R14.1, R15.1, R16.1, R17.1, R18.1, R19.1, R20.1, R21.1, R22.1, R23.1, U1.2 (VCC), U2.16 (VCC), U3.8 (VDD), U4.14 (VCC), U5.28 (VCC), U6.14 (VCC), U7.32 (VCC), U8.20 (VCC), U9.20 (VDD), U10.33 (VCC), U10.44 (VCC), U11.7 (VREGIN), X1.8 (Vcc)

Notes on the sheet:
ROM Write Override
RESET
